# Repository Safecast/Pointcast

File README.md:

# Pointcast V1.0
New generation nGeigie (work in progress)

Uploads are done through the gateway and go to http://dev.safecast.org

simple software setup:
  - arduino ide 
  - teensyduino or teensy application for uploading hex file into Teensy
  - upgrade firmware instructions are at https://docs.google.com/document/d/16hdhQj_UQkusotejkor8-5BlaK_a2mFPmyVPtsAJ4F8/edit?usp=sharing

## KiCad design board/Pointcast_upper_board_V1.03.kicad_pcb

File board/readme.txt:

Files are cretaed in Eagle software

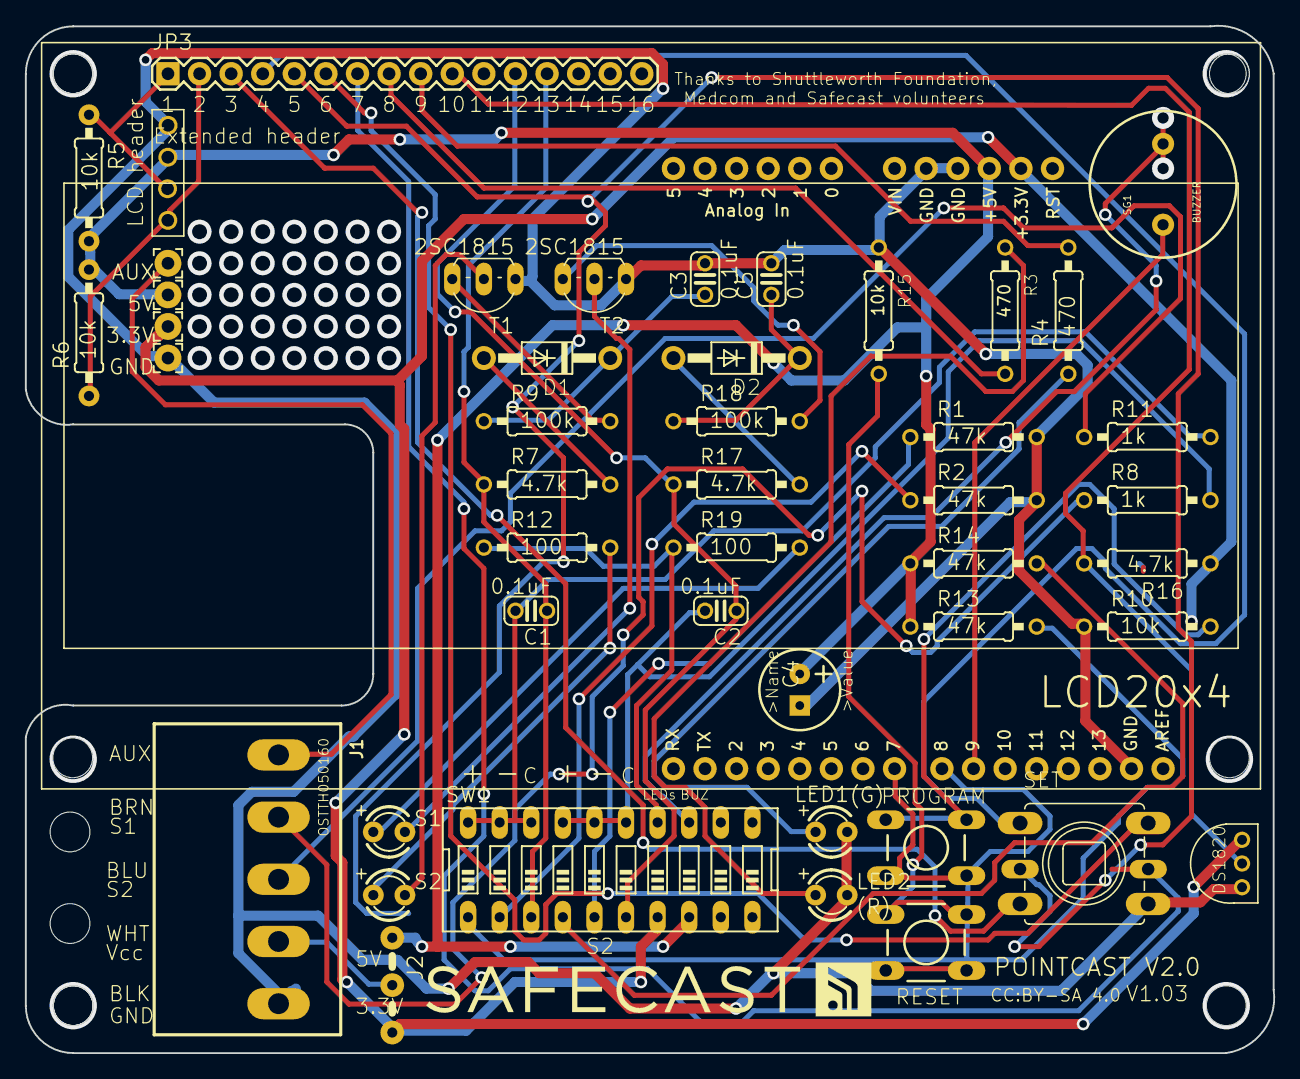
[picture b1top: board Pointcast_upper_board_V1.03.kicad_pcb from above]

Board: 2 copper layers, 100.4 x 82.6 mm, 56 parts (0 on the bottom side), 42 nets.

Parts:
@HOLE0, @HOLE1, @HOLE2, @HOLE3, @HOLE4, @HOLE5, @HOLE6: (no value)
C1, C2, C3, C5: 0.1uF; C025-024X044
C4: 100uf; CPOL-RADIAL-100UF-25V
D1, D2: DO41-10
FRAME1: FRAME-LEDGER; CREATIVE_COMMONS
J1: OSTTH050160; EDSTL130-05
J2: 04C
JP3: Extended header; 1X16
LED1: (G); LED3MM
LED2: (R); LED3MM
PAD1: AUX; 2,15%2f1,0
PAD2: 5V; 2,15%2f1,0
PAD3: GND; 2,15%2f1,0
PAD4: 3.3V; 2,15%2f1,0
PROGRAM: DTS-6
R1, R2, R13, R14: 47k; 0207%2f10
R3, R4: 470; 0207%2f10
R5, R6, R10, R15: 10k; 0207%2f10
R7, R16, R17: 4.7k; 0207%2f10
R8, R11: 1k; 0207%2f10
R9, R18: 100k; 0207%2f10
R12, R19: 100; 0207%2f10
RESET: RESET; DTS-6
S1, S2: LED3MM
SET: SKQU
SG1: BUZZER; BUZZER-12MM
SW1: EDG-10
T1, T2: 2SC1815; TO92-ECB
TEMP: AVA_DS1820TO92; AVA_DS1820
U$10: SAFECAST_LOGO1
X1: LCD-HD447804-HOLES20X4-4HOLES; LCD-20X4-4HOLES
X3: 3GS shield; DUEMILANOVE_SHIELD

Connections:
BLUE: J1.2, R8.1
BROWN: J1.3, R11.1
D14: C2.1, JP3.12, R17.1, SW1.6
D15: C1.1, JP3.13, R7.1, SW1.3
D17: JP3.3, SET.DOWN
D20: JP3.4, SET.UP
D21: JP3.5, SET.LEFT
D26: JP3.8, R3.2
D31: JP3.9, R4.2
D32: JP3.10, R16.2, TEMP.DQ
GND: C3.2, C4.1, C5.2, J1.5, LED1.K, LED2.K, PAD3.1, R1.2, R2.2, R10.1, R15.1, T1.E, T2.E, TEMP.GND, X1.P$13
unnamed: SG1.+, SW1.13
unnamed: LED2.A, R3.1
unnamed: R14.2, SW1.4
unnamed: R12.1, R19.1, SW1.14
unnamed: R2.1, SW1.2
unnamed: R1.1, SW1.5
unnamed: J1.1, PAD1.1
unnamed: SG1.-, X3.D9
unnamed: PROGRAM.1, PROGRAM.2, R10.2
unnamed: PROGRAM.3, PROGRAM.4, X3.D7
unnamed: J1.4, J2.2
unnamed: C1.2, R11.2, SW1.18, SW1.19, SW1.20
unnamed: R13.2, SW1.1
unnamed: D1.A, R7.2
unnamed: C3.1, D1.C, R9.1
unnamed: LED1.A, R4.1
unnamed: R9.2, T1.B
unnamed: S2.K, T1.C
unnamed: R15.2, RESET.1, RESET.2
unnamed: RESET.3, RESET.4, X3.D8
unnamed: R12.2, S2.A
unnamed: D2.A, R17.2
unnamed: C5.1, D2.C, R18.1
unnamed: R18.2, T2.B
unnamed: S1.K, T2.C
unnamed: R19.2, S1.A
unnamed: C2.2, R8.2, SW1.15, SW1.16, SW1.17
SCA: JP3.1, R5.1, X1.P$15
SCL: JP3.2, R6.1, X1.P$16
VCC: J2.3, PAD4.1, R16.1, SW1.7, TEMP.VDD, X3.3.3V
VDD: C4.2, J2.1, PAD2.1, R5.2, R6.2, R13.1, R14.1, SW1.8, X1.P$14, X3.5V

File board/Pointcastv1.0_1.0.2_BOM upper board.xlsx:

Part | Value | Device | Package | Description | MF | OC_ADAFRUIT | OC_MOUSER | OC_NEWARK
C1 | 0.1uF | C-EU025-024X044 | C025-024X044 | CAPACITOR, European symbol
C2 | 0.1uF | C-EU025-024X044 | C025-024X044 | CAPACITOR, European symbol
C3 | 0.1uF | C-EU025-024X044 | C025-024X044 | CAPACITOR, European symbol
C4 | 100uf | CAP_POLPTH1 | CPOL-RADIAL-100UF-25V | Capacitor Polarized
C5 | 0.1uF | C-EU025-024X044 | C025-024X044 | CAPACITOR, European symbol
D1 |  | DIODEDIODE_BIG | DO41-10 | Diode
D2 |  | DIODEDIODE_BIG | DO41-10 | Diode
FRAME1 | FRAME-LEDGER | FRAME-LEDGER | CREATIVE_COMMONS | Schematic Frame
J1 | OSTTH050160 | OSTTH050160 | EDSTL130-05 | 5mm Terminal Header
JP3 | Extended header | M16PTH | 1X16 | 1x16 .1 header"
LED1 | (G) | LED3MM | LED3MM | LED
LED2 | (R) | LED3MM | LED3MM | LED
PAD1 | AUX | 2,15/1,0 | 2,15/1,0 | THROUGH-HOLE PAD
PAD2 | 5V | 2,15/1,0 | 2,15/1,0 | THROUGH-HOLE PAD
PAD3 | GND | 2,15/1,0 | 2,15/1,0 | THROUGH-HOLE PAD
PAD4 | 3.3V | 2,15/1,0 | 2,15/1,0 | THROUGH-HOLE PAD
R1 | 47k | R-US_0207/10 | 0207/10 | RESISTOR, American symbol
R2 | 47k | R-US_0207/10 | 0207/10 | RESISTOR, American symbol
R3 | 470 | R-US_0207/10 | 0207/10 | RESISTOR, American symbol
R4 | 470 | R-US_0207/10 | 0207/10 | RESISTOR, American symbol
R5 | 10k | R-US_0207/10 | 0207/10 | RESISTOR, American symbol
R6 | 10k | R-US_0207/10 | 0207/10 | RESISTOR, American symbol
R7 | 4.7k | R-US_0207/10 | 0207/10 | RESISTOR, American symbol
R8 | 1k | R-US_0207/10 | 0207/10 | RESISTOR, American symbol
R9 | 100k | R-US_0207/10 | 0207/10 | RESISTOR, American symbol
R11 | 1k | R-US_0207/10 | 0207/10 | RESISTOR, American symbol
R12 | 100 | R-US_0207/10 | 0207/10 | RESISTOR, American symbol
R13 | 47k | R-US_0207/10 | 0207/10 | RESISTOR, American symbol
R14 | 47k | R-US_0207/10 | 0207/10 | RESISTOR, American symbol
R15 | 10k | R-US_0207/10 | 0207/10 | RESISTOR, American symbol
R16 | 4.7k | R-US_0207/10 | 0207/10 | RESISTOR, American symbol
R17 | 4.7k | R-US_0207/10 | 0207/10 | RESISTOR, American symbol
R18 | 100k | R-US_0207/10 | 0207/10 | RESISTOR, American symbol
R19 | 100 | R-US_0207/10 | 0207/10 | RESISTOR, American symbol
RESET | RESET | DTS-6 | DTS-6
S1 |  | LED3MM | LED3MM | LED
S2 |  | LED3MM | LED3MM | LED
SET |  | SKQUCAA010 | SKQU | Multi Control Devices TACT Switch - 4-directional with Center Push Type. | ALPS | 504 | 688-SKQUCA | 59M1983
SG1 | BUZZER | BUZZERPTH | BUZZER-12MM | Buzzer 12mm
SW1 |  | SW_DIP-10 | EDG-10 | DIP SWITCH
T1 | 2SC1815 | 2SC1815 | TO92-ECB | NPN EPITAXIAL TRANSISTOR
T2 | 2SC1815 | 2SC1815 | TO92-ECB | NPN EPITAXIAL TRANSISTOR
TEMP | AVA_DS1820TO92 | AVA_DS1820TO92 | AVA_DS1820 | DS18B20
X1 | LCD-HD447804-HOLES20X4-4HOLES | LCD-HD447804-HOLES20X4-4HOLES | LCD-20X4-4HOLES
X3 | 3GS shield | ARDUINO_SHIELDLABEL | DUEMILANOVE_SHIELD | Arduino shield footprint

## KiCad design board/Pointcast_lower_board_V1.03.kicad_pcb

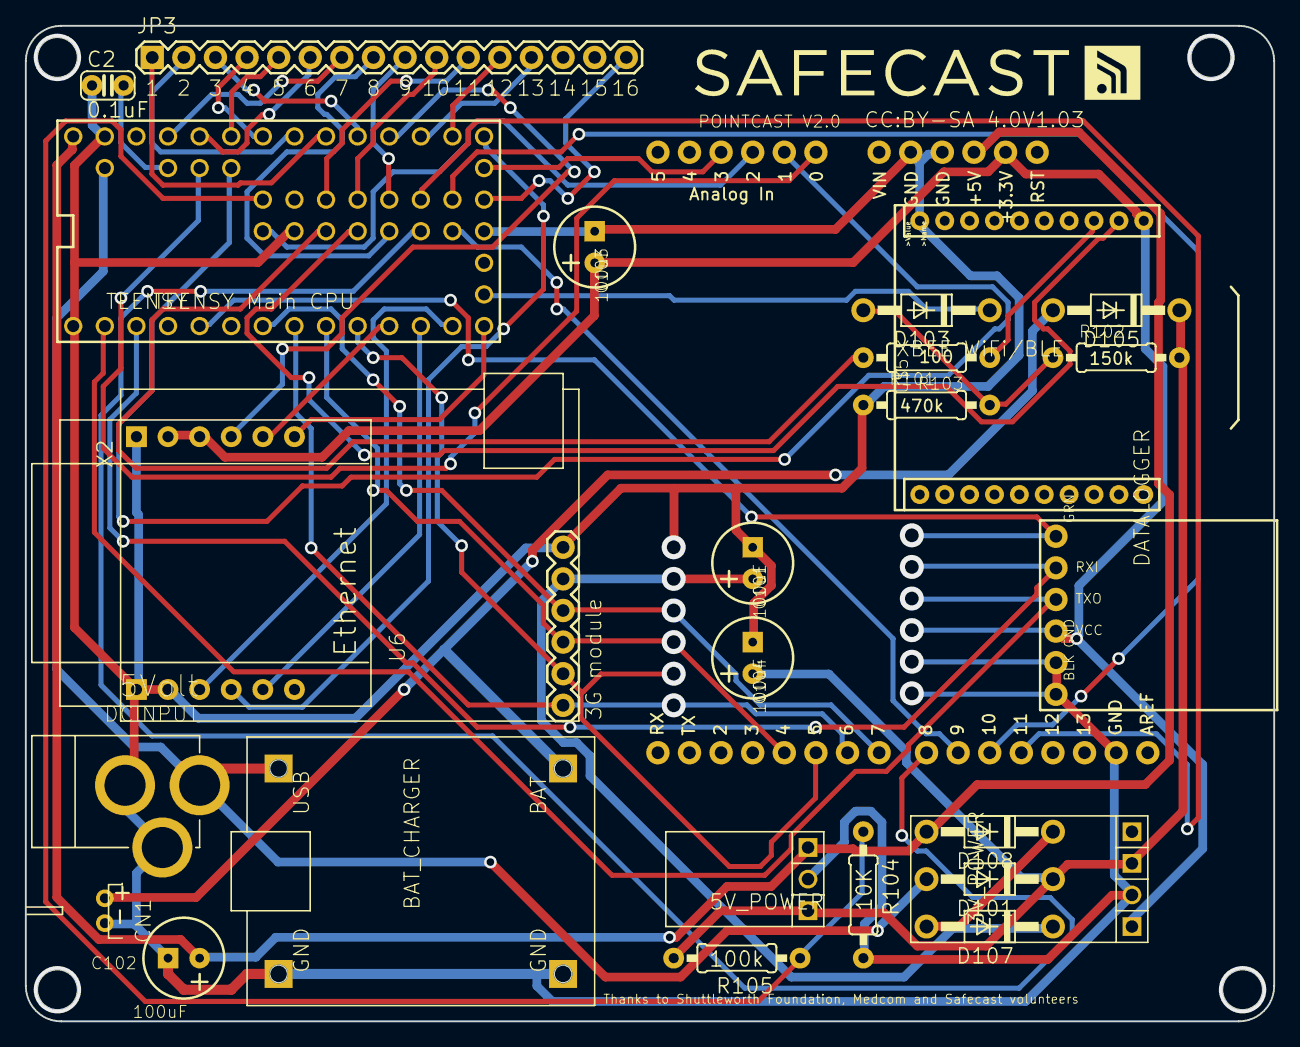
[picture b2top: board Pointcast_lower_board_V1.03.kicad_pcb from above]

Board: 2 copper layers, 100.3 x 80.0 mm, 33 parts (0 on the bottom side), 36 nets.

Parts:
3V_POWER: POLOLU_D24VXAYV_HC
5V_POWER: POLOLU_S7V8F5
@HOLE0, @HOLE1, @HOLE2, @HOLE3: (no value)
BAT_CHARGER: TP4056_CHARGER; TP4056
C2: 0.1uF; C025-024X044
C101, C102, C103, C104: 100uF; CPOL-RADIAL-100UF-25V
CN1: JST-PH-2-THM-RA
D101, D103, D105, D107, D108: 1N4004; DO41-10
DATALOGGER: OPENLOG
DCINPUT: 5Volt; DC-21MM
FRAME1: FRAME-LEDGER; CREATIVE_COMMONS
JP3: 1X16
R101: 470k; 0207%2f10
R102: 150k; 0207%2f10
R103: 100; 0207%2f10
R104: 10K; 0207%2f10
R105: 100k; 0207%2f10
TEENSY: TEENSY Main CPU; TEENSY_3.0_ALLPINS
U6: Ethernet; WIZ820IO
U$5: XBEE WiFi/BLE; XBEE-SILK
U$10: SAFECAST_LOGO1
X2: 3G module; 1X06
X4: 3GS shield; DUEMILANOVE_SHIELD

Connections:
A10: TEENSY.A10, X4.A0
A11: TEENSY.A11, X4.A1
A12: TEENSY.A12, X4.A2
BAT: BAT_CHARGER.BAT, CN1.1, D105.A
D5: TEENSY.5, X2.4, X4.D7
D6: TEENSY.6, X2.1, X4.D6
D7: TEENSY.7, X2.3, X4.D4
D8: TEENSY.8, X2.2, X4.D5
D9: TEENSY.9, U6.J2.5
D10: TEENSY.10, U6.J1.5
D11: TEENSY.11, U6.J1.3
D12: TEENSY.12, U6.J2.6
D13: TEENSY.13, U6.J1.4
D26: JP3.8, TEENSY.26
D27: TEENSY.27, X4.D8
D28: TEENSY.28, X4.D9
D29: TEENSY.29, X4.D10
D30: TEENSY.30, X4.D11
D31: JP3.9, TEENSY.31
D32: JP3.10, TEENSY.32
D33: JP3.11, TEENSY.33
GND: 3V_POWER.G, 5V_POWER.G, BAT_CHARGER.GND, BAT_CHARGER.GND2, C2.1, C101.1, C102.1, C103.1, C104.1, CN1.2, DCINPUT.1, DCINPUT.3, R101.1, R104.2, TEENSY.AGND, TEENSY.GND, TEENSY.GND1, TEENSY.GND2, U6.J1.1, U6.J1.2, U6.J2.1, U$5.10, X2.6
unnamed: D103.C, TEENSY.VBAT
unnamed: D103.A, R101.2, R102.1
unnamed: R104.1, R105.1, TEENSY.A13
unnamed: R103.1, U$5.3
unnamed: C2.2, TEENSY.AREF
unnamed: D107.A, D108.C
unnamed: C101.2, D107.C, X2.5
PGM: JP3.16, TEENSY.PGM
PWRIN: 3V_POWER.I, 5V_POWER.I, C104.2, D101.C, D105.C, R102.2, R105.2
RXI: TEENSY.25, U$5.2
TXO: R103.2, TEENSY.24
VCC: 3V_POWER.O, C103.2, U6.J2.2, U6.J2.3, U$5.1, X4.3.3V
VDD: 5V_POWER.O, C102.2, D108.A, TEENSY.VIN, X4.5V
VUSB: D101.A, DCINPUT.2, TEENSY.VUSB

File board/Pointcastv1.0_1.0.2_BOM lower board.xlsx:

Part | Value | Device | Package | Description | PROD_ID
3V_POWER |  | POLOLU_D24V3AXV | POLOLU_D24VXAYV_HC | Pololu Adjustable Step Down Voltage Regulators Series D24V3A_V (300 mA)0.4x0.6""
5V_POWER |  | POLOLU_S7V8F5 | POLOLU_S7V8F5 | POLOLU_S7V8F5
BAT_CHARGER | TP4056_CHARGER | TP4056_CHARGER | TP4056 | TP4056
C2 | 0.1uF | C-EU025-024X044 | C025-024X044 | CAPACITOR, European symbol
C101 | 100uF | CAP_POLPTH1 | CPOL-RADIAL-100UF-25V | Capacitor Polarized
C102 | 100uF | CAP_POLPTH1 | CPOL-RADIAL-100UF-25V | Capacitor Polarized
C103 | 100uF | CAP_POLPTH1 | CPOL-RADIAL-100UF-25V | Capacitor Polarized
C104 | 100uF | CAP_POLPTH1 | CPOL-RADIAL-100UF-25V | Capacitor Polarized
CN1 |  | JST_2PIN-THM-RA | JST-PH-2-THM-RA | JST 2-Pin Connectors of various flavors
D101 | 1N4004 | 1N4004 | DO41-10 | DIODE
D103 | 1N4004 | 1N4004 | DO41-10 | DIODE
D105 | 1N4004 | 1N4004 | DO41-10 | DIODE
D107 | 1N4004 | 1N4004 | DO41-10 | DIODE
D108 | 1N4004 | 1N4004 | DO41-10 | DIODE
DATALOGGER | OPENLOG | OPENLOG | OPENLOG | Openlog
DCINPUT | 5Volt | DC21MMX | DC-21MM
FRAME1 | FRAME-LEDGER | FRAME-LEDGER | CREATIVE_COMMONS | Schematic Frame
JP3 |  | M16PTH | 1X16 | 1x16 .1 header"
R101 | 470k | R-US_0207/10 | 0207/10 | RESISTOR, American symbol
R102 | 150k | R-US_0207/10 | 0207/10 | RESISTOR, American symbol
R103 | 100 | R-US_0207/10 | 0207/10 | RESISTOR, American symbol
R104 | 10K | R-US_0207/10 | 0207/10 | RESISTOR, American symbol
R105 | 100k | R-US_0207/10 | 0207/10 | RESISTOR, American symbol
TEENSY | TEENSY Main CPU | TEENSY_3.0_ALLPINS | TEENSY_3.0_ALLPINS | Teensy 3.0 with all pin holes and optional SMD-mount unshrouded header on botto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
U$5 | XBEE WiFi/BLE | XBEE-2B2 | XBEE-SILK | Xbee module footprints
U6 | Ethernet | WIZ820IO_DEVICE'DUAL-IN-LINE' | WIZ820IO | WIZnet, WIZ820io plug in module incl. W5200 chip and MagJack
X2 | 3G module | M06SILK_FEMALE_PTH | 1X06 | Header 6 | CONN-08437
X4 | 3GS shield | ARDUINO_SHIELDLABEL | DUEMILANOVE_SHIELD | Arduino shield footprint

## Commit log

2015-02-28 initial project version
2015-03-03 Fixed dual upload and interupt routine deleted displaying pulses.
2015-03-03 Added zipped hex file
2015-03-03 Changed time for sending to 5 minutes.
2015-03-03 Version change
2015-03-03 And the compressed hex file
2015-03-03 Changed display messages
2015-03-03 layout of display changed
2015-03-05 Pull up active on inputs inputs are setup for falling edge
2015-03-07 Added upldated Hex file
2015-03-07 renamed Hex zip file
2015-03-09 Added libraries and new boards
2015-03-09 Added more files
2015-03-09 Update I2C library and added Hex file
2015-03-09 Added Gerber files
2015-03-09 Cleaned up code, added final boards.
2015-04-01 Create gh-pages branch via GitHub
2015-04-04 Added reset to A14
2015-04-05 Added LED check on startup..
2015-04-06 LED delay setup
2015-04-07 Code for Ethetnet and 3G combined
2015-04-07 Send and recieve every 5 minutes. (2.6.1 was every 5 seconds for stress testing)
2015-04-09 Switch between DEV and API sending the data...
2015-04-13 added switch for switching from Ethernet and other options to switch in the coding without recompile.
2015-04-13 Added heart beat on green LED every 10 seconds..
2015-04-14 Switched back to two compile versions(3G and Ethernet) and added setup variables
2015-04-14 Added extra setup files
2015-04-21 V2.6.8 added device ID, startup screen change, header for file format changed to NGRDD
2015-04-23 Sensor header added as second line on SDcard
2015-04-27 Changed name repro
2015-04-27 changed name
2015-04-27 And all the other files updated to Pointcast
2015-04-27 More files
2015-04-27 Version named too..
2015-04-27 Added latest boards
2015-04-27 And the boards
2015-04-30 Added temperature setup for DS18B20 (disabled at the moment) setup screens
2015-05-02 V2.7.3 Added joystick setup functions, cleanup code
2015-05-04 Added height info
2015-05-04 Fixed lot/lan sending information on Ethernet
2015-05-07 V2.7.3 with SDCard files corrected..
2015-05-07 Display SDCard errors was disabled.. Now enbaled.
2015-05-08 V2.7.4 More screens and error reporting.
2015-05-10 Renaming and 3G display screen setup
2015-05-10 Added sdcard files
2015-05-14 BOM updated
2015-05-16 V2.7.9 Added Joystick interaction. Key down startup 1/5 of normal time. Prepare joy stick enter ket (push down) for other functions.
2015-05-16 Extra files added
2015-05-18 Automatic time setup on Ethernet NTP
2015-05-19 Fixes for 3G after RTC updates (RTC for 3G not setup yet)
2015-05-20 Added random auto gateway , added fast troubleshooting mode
2015-05-22 Added "trb=0" option to the sdcard setup be able to fast trouble shoot the senor
2015-05-24 Modified 3GIM library for faster access.
2015-05-24 And the files
2015-05-24 Added the missing version number
2015-05-31 Interactive menu fixes.
2015-06-05 V2.9.1. updated for loud buzzer and fast sensing setup select from SDcard
2015-06-07 Temperature setup, APIKEY display, battery/power updated
2015-06-07 Added .gitignore
2015-06-09 Temperature fix and some display changes.
2015-06-17 Fixes for sdcard temp and battery, file naming, etc
2015-06-20 V2.9.8 Switch between API and DEV by sdcard setting (dev=1 for sending data to dev.safecast.org)
2015-06-22 V2.9.9 DEV status on LCD
2015-06-22 V3.0.0 Fix second line
2015-06-27 V3.0.2 Height added
2015-07-01 V3.0.4 fixed for diagnostics/RTC and network setup
2015-08-15 V3.07 fixed dsiplay bug for Ethernet
2015-08-18 Changed voltage display to compansate for voltage drop over D103
2015-08-20 Switched Teensy to intrenal reference mode 1.2V
2015-08-25 Ethernet MAC setup from SDCARD
2015-08-25 Imporved SD card fail logic
2015-08-25 Added Carrier display for 3G and change voltage display with no diode compensation
2015-08-25 Modified Mac display to be always how two digits
2015-09-02 Add libs
2015-09-02 And the rest of the files
2015-09-03 Added missing libs
2015-09-06 V3.2.4 misc fixes
2015-09-11 V3.2.5 changed FAILS display in 3G and Ethernet
2015-09-18 Added documentions
2015-09-19 V3.2.8 Added single sensor not faling on test
2015-09-28 Weekly reset setup
2015-09-28 Added correct version number
2015-10-03 Weekly reset and 3 beeps before restart. On boot two beeps
2015-10-22 Misc fixes V3.3.2
2015-11-12 Changed the way 3G connects to APN
2015-11-16 V3.3.5 Eeprom cleared on pressing enter key of Joystick at start menu.
2015-11-17 V3.3.6 added reset failure LED by enter (push down) joyswitch
2015-11-19 More fixes display
2015-12-11 V3.4.0 EEprom storage
2015-12-16 3G connect fail error display fixes.
2016-01-01 V3.4.2 Fixed Ethernet display
2016-01-05 Change network parameters for 3G
2016-01-18 Added massages for connect with httpPOST 3G
2016-01-24 Added extra code for different temperature sensors.
2016-01-26 Changed way to send data for 3G ..powerup-send-powerdown...
2016-02-01 Setup alarm
2016-02-15 Added retries 3 time to 3G and hard reset.
2016-02-18 Added reply messages for API to display on treminal screen.
2016-02-19 Cleaned up formatting
2016-02-20 Fixes for Ethernet time issues and time sending to API
2016-02-21 Fixes for timezone and lockups
2016-03-02 V3.6.0 fixed Ethernet not connected
2016-03-05 Fixes for timestaming.
2016-03-06 Daily restarts
2016-03-06 V3.6.5 Fixed another time bug.
2016-03-08 V3.6.6 Cleaned out debug code
2016-03-09 V 3.6.7 Added test for pinging network in Ethernet and 3G mode in startup
2016-03-10 V3.6.8 added ping menus, RTC menu and build logic for menu
2016-03-11 V3.6.8 implemented ping menu, added documentation
2016-03-11 Added extra docs.
2016-03-11 More docs.
2016-03-11 V3.7.0 ping tests for 3G and Ethernet setup.
2016-03-13 V3.7.1 redone screenflow
2016-03-13 V3.7.1 GW02/GW02 setup -ping Google.com
2016-03-14 V3.7.4 display time remaing to sent and ping setup to s3
2016-03-17 V3.7.7 create log entries are stored in EEProm
2016-03-27 V3.7.8 added temperature on main screen, dev and api switch on display, logging header with logs, retarts and fails
2016-03-28 V3.7.9 Fixed after EEprom errase no counting error.
2016-03-31 Pointcast for Hosting People JP.pdf
2016-04-17 Use push key to stop display screen for 100 seconds
2016-04-19 V3.8.2 Added pause at screens.
2016-04-22 V 3.8.3 Fix for starting at always on 5 minutes count down.
2016-04-27 V3.8.4 disbaled adaptive counting
2016-04-29 V3.8.6 added phone number setup from sdcard for 3G, changed display data to 1 minute, changed NX to 12 and delay to 5000 for 5 seconds measuring, KCPM 2 charater after decimal point
2016-04-29 V3.8.7 added \n to new log file to keep data separated from comment.
2016-05-05 V3.8.8 display silding window data every 5 minutes only
2016-05-05 Added Kicad files for V1.03 board
2016-05-15 V3.8.9 DNS setup for NTP timeserver (before hardcoded to pool.ntp.org)
2016-05-15 V3.9.0 Xbee setup
2016-05-21 V3.9.1 Menu fixed in 3G and Ethernet.
2016-06-09 V3.9.2 Added FreeRam on display, serial out and on sdcard.
2016-06-17 V3.9.4 Cocde clean and 5 minutes count from all bins.
2016-07-07 V3.9.5 Ethernet reset before startup.
2016-07-08 V3.9.6 Weekly reset init moved after TeensClock is set.
2016-07-12 V3.9.6 Ethernet hex file
2016-07-12 V3.9.6 3G hex file
2016-07-16 V3.9.7 Added interruptCounterReset() just before count starts
2016-07-21 V3.9.8 true random minutes at weekly restarts.
2016-07-22 V3.9.8 3G fixed weekly restats to be randowm within one hour
2016-07-27 V3.9.9 fixed for DS18S20 sensor.
2016-07-27 V4.0.0 adjusted display for ethernet and 3G to display count down in 4 digits and get even spaces for the voltage and temperature.
2016-07-29 V4.0.2 Misc 3G and Ethernet connection changes
2016-08-01 V4.0.3 improved weekly restart based on rst value on sdcard
2016-08-01 Added link update firmware
2016-08-03 Added Hex files
2016-08-03 Added files
2016-08-10 V4.0.5 moved 3GIM powerdown/up closer to startup to give 3GIM module more time settle down before startup
2016-08-28 Added holes for glands placement for Ethernet
2016-08-28 Updated holes pictures
2016-08-29 V4.0.6 fixes Ethernet S1 LED problem.
2016-09-09 V4.0.7 fixed retries Ethernet
2016-09-09 V4.0.8 added 3 seconds delay between retries Ethernet
2016-09-15 V4.0.9 fixes for NTP server (Ray suggestions)
2016-09-17 V4.1.1 weekly reset redone, failure messages on SDcard, misc fixes
2016-09-18 V4.1.2 many warnings from compiler fixes.
2016-09-18 V4.1.3 NTP timeout of retries to server 5 minutes.
2016-09-20 V4.1.4 Fixed temp sensor
2016-09-22 V4.1.5 clened up formating
2016-09-22 V4.1.6 setup NTP check for 15 seconds retries and 300 seconds timeout
2016-09-23 V4.1.7 setup to renew a lease for DHCP every 5 minutes for networks that have short DHCP lease setup
2016-10-07 Added app folder for Mac uploader app with newest firmware for 3G and Ethernet
2016-10-07 Zipped the apps for easy downlaoding from github.
2016-10-07 And added the zips.
2016-10-17 V4.1.9 addded confirmation of measurement_id recieved by API.
2016-10-27 V4.2.0 Added status reporting to API.
2016-10-27 V4.2.1 Fix for Ethernet Status sending
2016-10-29 V4.2.2 display measurements_id in terminal display in Ethernet mode
2016-10-31 V4.2.3 Fixed 3G for send display
2016-11-05 V4.2.3 with hex and app files added.
2016-11-08 Added correct drill template box and sdcard configs zipped
2016-11-13 V4.2.4 3G error messages on fail fix.
2016-11-21 Added teensy.exe for windows teensy flashing
2016-11-21 Change the Teensy.exe for zipped version
2016-11-25 Added docs for updating firmware for windows in english and japanese.
2016-12-10 Updated hole placement for case.
2017-02-13 V4.2.5 SDcard edit with Windows text edittor fix.
2018-05-16 test
2018-05-16 removed test
2018-06-02 Fixed reading cr/lf for sdcard reading (honor goes to Ray)
2018-06-02 Added version update
2018-09-05 test for Ethernet 2 version
2018-09-05 Added correct libraries
2018-09-05 Added more libraries
